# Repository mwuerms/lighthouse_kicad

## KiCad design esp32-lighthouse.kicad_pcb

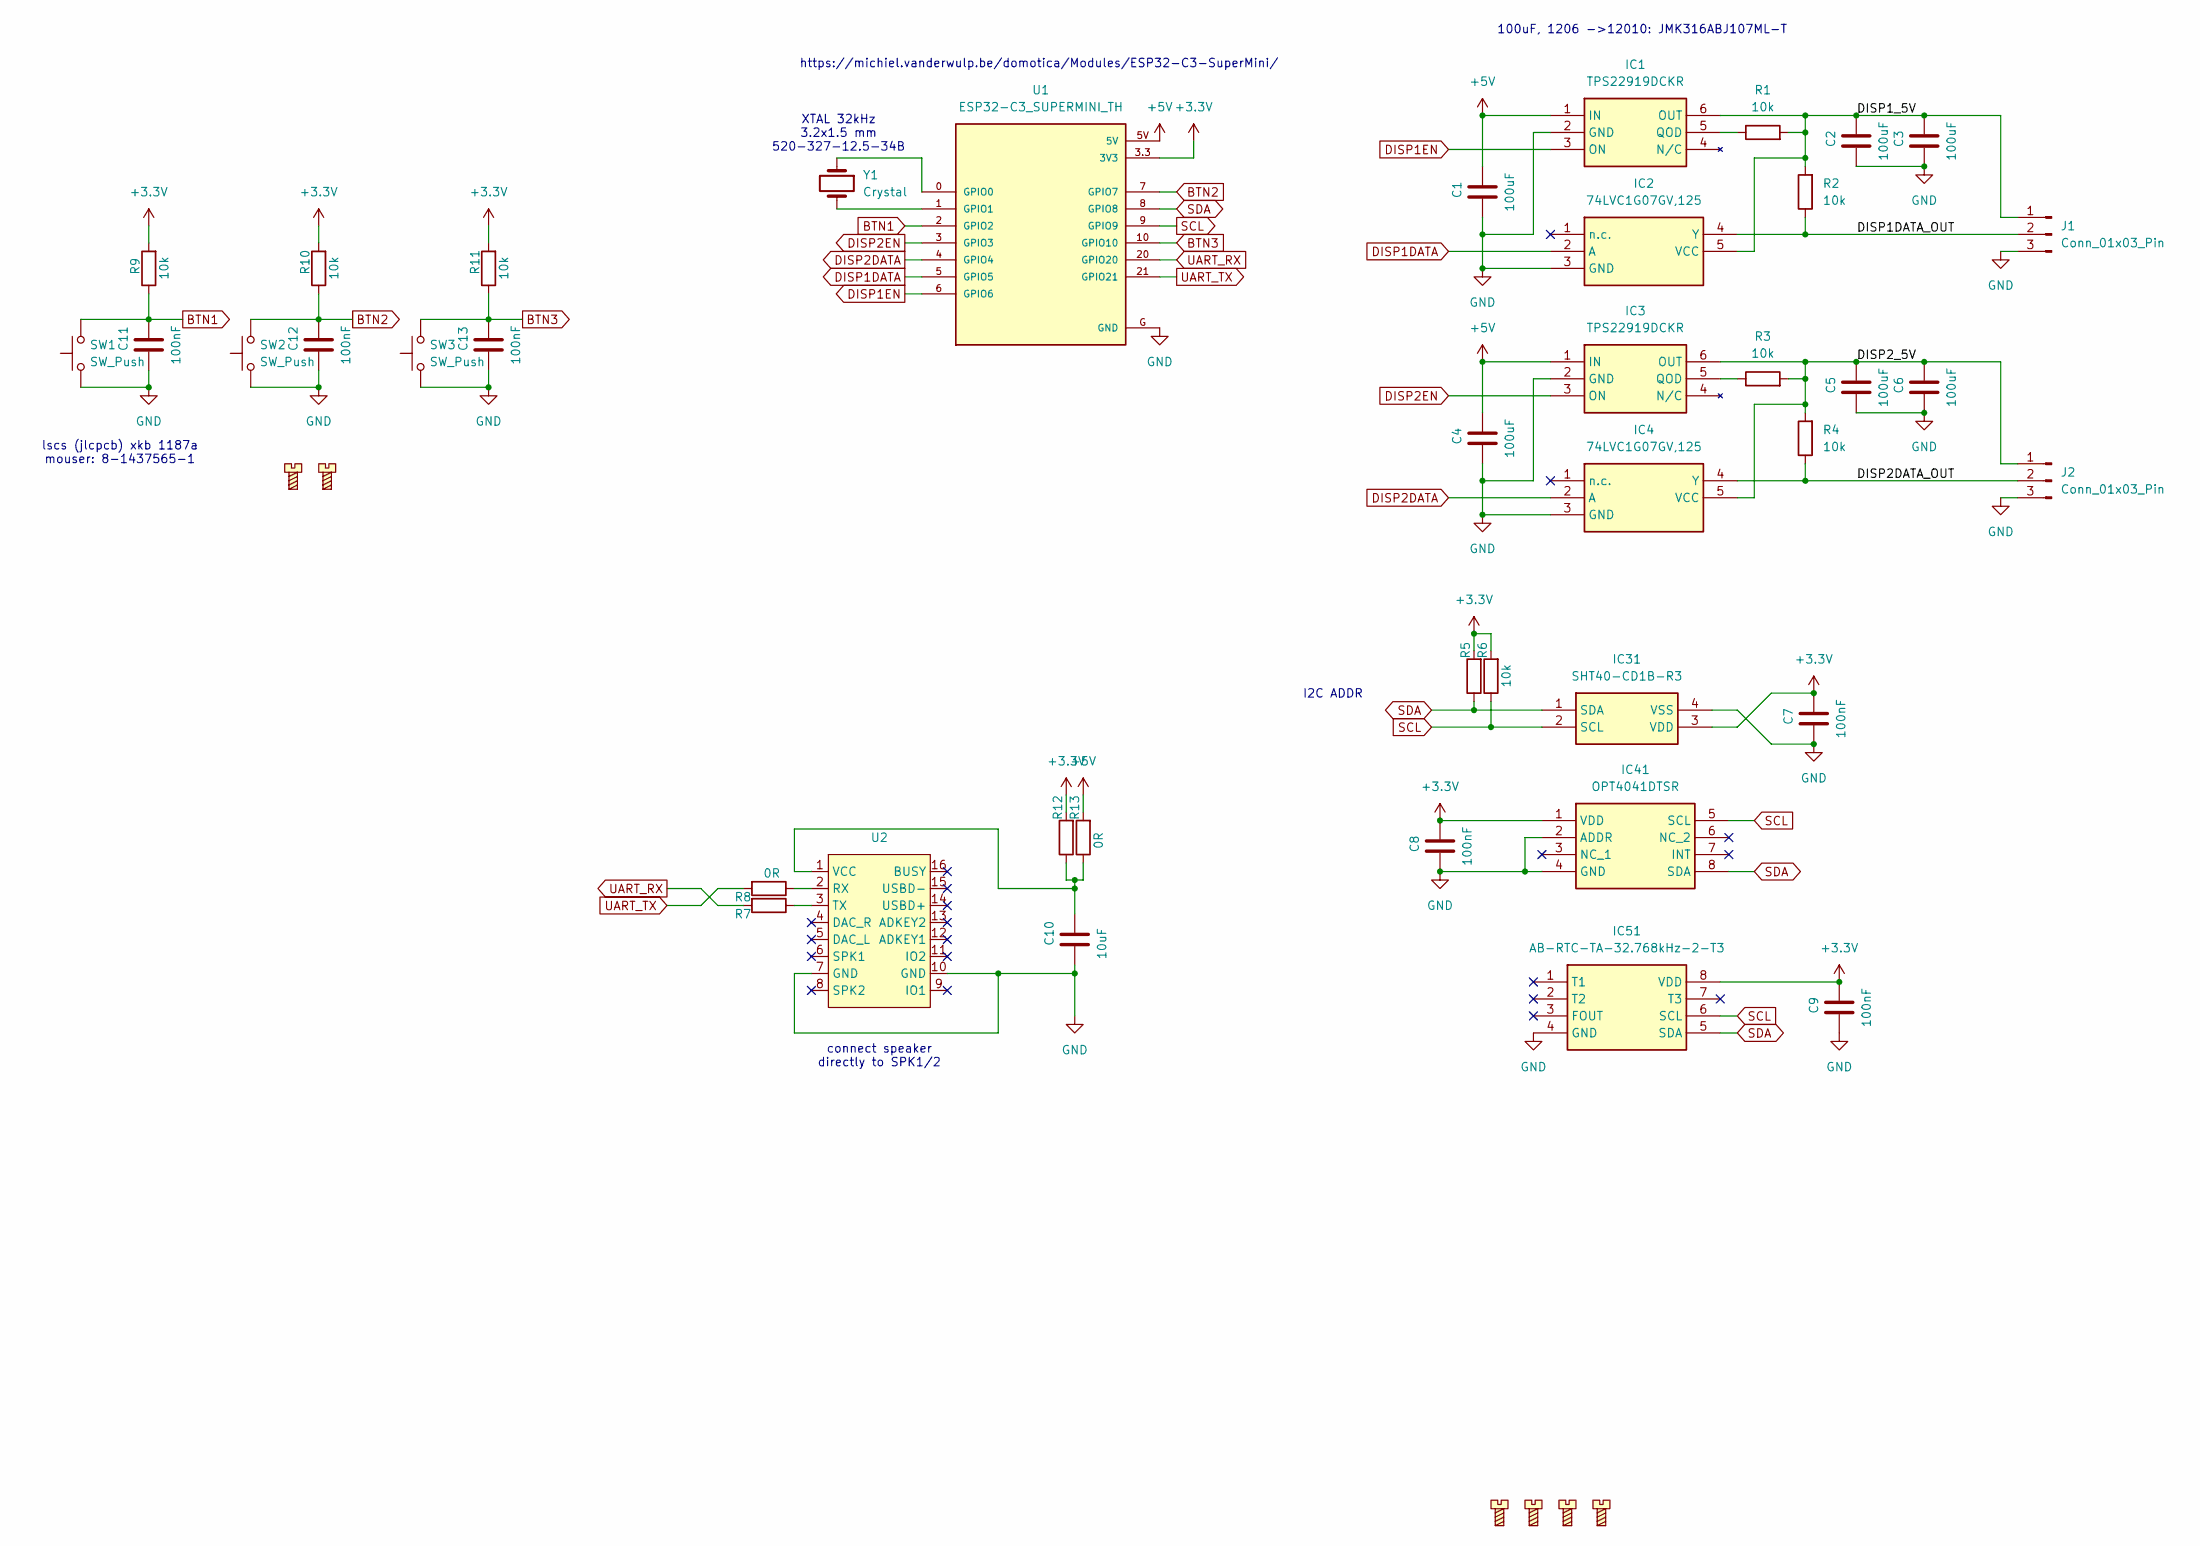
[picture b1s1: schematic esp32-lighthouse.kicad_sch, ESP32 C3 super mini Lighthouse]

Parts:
C1, C2, C3, C4, C5, C6: 100uF; C_1210_3225Metric
C7, C8, C9, C11, C12, C13: 100nF; C_0603_1608Metric
C10: 10uF; C_1210_3225Metric
H1, H2, H3, H4, H5, H6: Mounting_Screw; M3Hole
IC1, IC3: TPS22919DCKR; SOT65P210X110-6N; Mouser Part Number 595-TPS22919DCKR
IC2, IC4: 74LVC1G07GV,125; SOT95P275X110-5N; Mouser Part Number 771-74LVC1G07GV
IC31: SHT40-CD1B-R3; SHT40CD1BR3; Mouser Part Number 403-SHT40-CD1B-R3
IC41: OPT4041DTSR; SOTFL50P190X60-8N; Manufacturer_Part_Number OPT4041DTSR
IC51: AB-RTC-TA-32.768kHz-2-T3; SOIC127P620X180-8N; Manufacturer_Part_Number AB-RTC-TA-32.768kHz-2-T3
J1, J2: Conn_01x03_Pin; H3_100mil
R1, R2, R3, R4, R5, R6, R9, R10, R11: 10k; R_0603_1608Metric
R7, R8, R12, R13: 0R; R_0603_1608Metric
SW1, SW2, SW3: SW_Push; SW_Push_1P1T_XKB_TS-1187A
U1: ESP32-C3_SUPERMINI_TH; MODULE_ESP32-C3_SUPERMINI_TH
U2: DFPlayer_Mini-TF-16P
Y1: Crystal; Crystal_SMD_3215-2Pin_3.2x1.5mm

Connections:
+3.3V: C7.1, C8.1, C9.1, IC31.3 (VDD), IC41.1 (VDD), IC51.8 (VDD), R5.2, R6.2, R9.2, R10.2, R11.2, R12.2, U1.3.3 (3V3)
+5V: C1.1, C4.1, IC1.1 (IN), IC3.1 (IN), R13.2, U1.5V
/DISP1DATA_OUT: IC2.4 (Y), J1.2, R2.1
/DISP1_5V: C2.1, C3.1, IC1.6 (OUT), IC2.5 (VCC), J1.1, R1.2, R2.2
/DISP2DATA_OUT: IC4.4 (Y), J2.2, R4.1
/DISP2_5V: C5.1, C6.1, IC3.6 (OUT), IC4.5 (VCC), J2.1, R3.2, R4.2
BTN1: C11.1, R9.1, SW1.2, U1.2 (GPIO2)
BTN2: C12.1, R10.1, SW2.2, U1.7 (GPIO7)
BTN3: C13.1, R11.1, SW3.2, U1.10 (GPIO10)
DISP1DATA: IC2.2 (A), U1.5 (GPIO5)
DISP1EN: IC1.3 (ON), U1.6 (GPIO6)
DISP2DATA: IC4.2 (A), U1.4 (GPIO4)
DISP2EN: IC3.3 (ON), U1.3 (GPIO3)
GND: C1.2, C2.2, C3.2, C4.2, C5.2, C6.2, C7.2, C8.2, C9.2, C10.2, C11.2, C12.2, C13.2, IC1.2 (GND), IC2.3 (GND), IC3.2 (GND), IC4.3 (GND), IC31.4 (VSS), IC41.2 (ADDR), IC41.4 (GND), IC51.4 (GND), J1.3, J2.3, SW1.1, SW2.1, SW3.1, U1.G (GND), U2.7 (GND), U2.10 (GND)
unnamed: IC1.5 (QOD), R1.1
unnamed: IC3.5 (QOD), R3.1
unnamed: U1.0 (GPIO0), Y1.1
unnamed: U1.1 (GPIO1), Y1.2
unnamed: R8.1, U2.2 (RX)
unnamed: R7.1, U2.3 (TX)
unnamed: C10.1, R12.1, R13.1, U2.1 (VCC)
SCL: IC31.2 (SCL), IC41.5 (SCL), IC51.6 (SCL), R6.1, U1.9 (GPIO9)
SDA: IC31.1 (SDA), IC41.8 (SDA), IC51.5 (SDA), R5.1, U1.8 (GPIO8)
UART_RX: R7.2, U1.20 (GPIO20)
UART_TX: R8.2, U1.21 (GPIO21)

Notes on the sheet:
https://michiel.vanderwulp.be/domotica/Modules/ESP32-C3-SuperMini/
I2C ADDR
100uF, 1206 ->12010: JMK316ABJ107ML-T
lscs (jlcpcb) xkb ‎1187a mouser: 8-1437565-1
XTAL 32kHz 3.2x1.5 mm 520-327-12.5-34B
connect speaker directly to SPK1/2

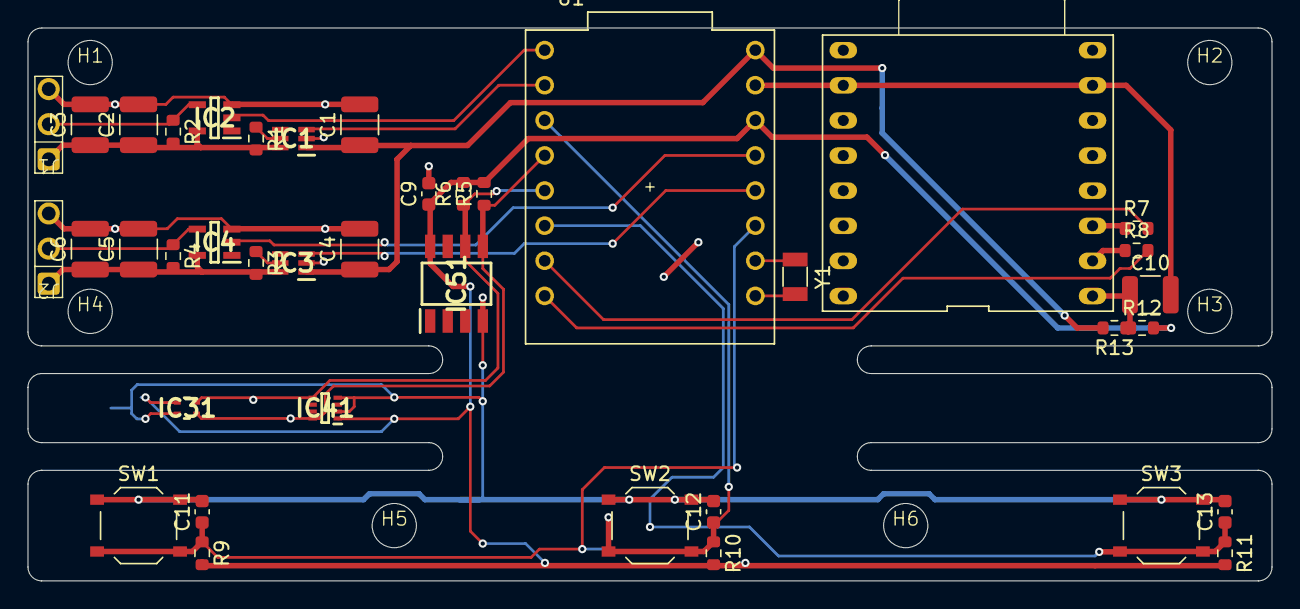
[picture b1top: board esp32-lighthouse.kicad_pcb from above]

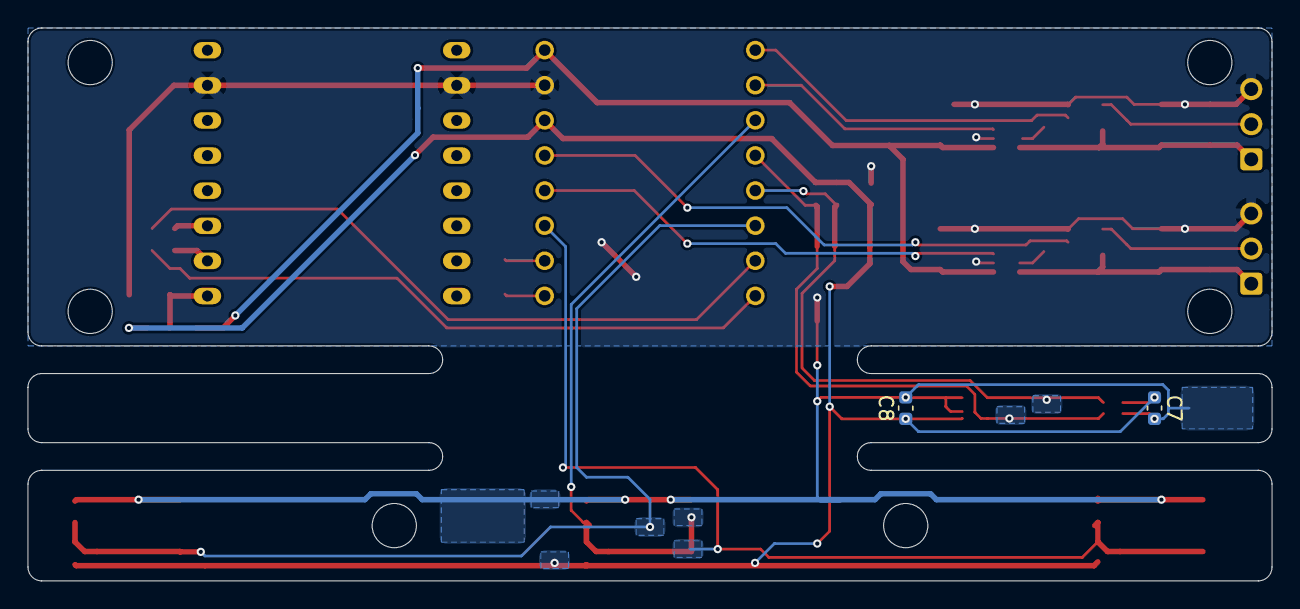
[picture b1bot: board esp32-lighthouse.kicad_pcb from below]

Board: 2 copper layers, 90.0 x 40.0 mm, 47 parts (2 on the bottom side), 25 nets.
